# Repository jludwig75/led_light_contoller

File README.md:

# LED Light Controller #
This is a simple controller for for cheap 2-wire LED strings. These strings are setup with LED's alternating polarity along the two wires. Current inone direction lights every other LED and current in the other direction lights the other LED's in the string. These LED strings are really cheap and often sold with remote controls to control the lighting. The battery life is terrible and the light patterns selections weren't that great. I wrote this Arduino sketch for and ESP8266 to control the LED strings. I am using ESP8266 breakouts from Electrodragon that include a USB port for programming and power. I am also using a DRV8833 H-bridge to controll the LED's powered by the 5V pin from the USB connector to the Electordragon board.

The sketch includes a web server used to controll the light pattern. Each board controls two strings (channels) independently. Note that the sketch is written to switch polarity every 10ms (100Hz). This allows the strings to appear to be contantly lit in both directions.

## Components  ##
- Electrodragon board link: https://www.electrodragon.com/product/esp8266-smd-adapter-breakout-board-r3/
- DRV8833 Link: https://www.amazon.com/gp/product/B08FJ3TX3Z/ref=ppx_yo_dt_b_asin_title_o01_s00?ie=UTF8&psc=1
- LED Light Strings: https://www.amazon.com/gp/product/B07QC65SZP/ref=ppx_yo_dt_b_asin_title_o04_s00?ie=UTF8&psc=1

## Schematic ##

## PCB Board ##

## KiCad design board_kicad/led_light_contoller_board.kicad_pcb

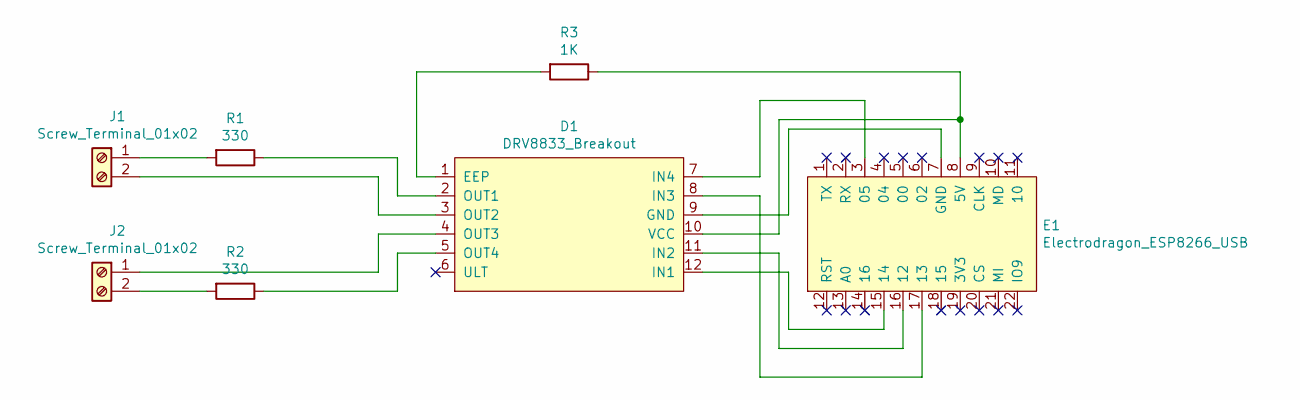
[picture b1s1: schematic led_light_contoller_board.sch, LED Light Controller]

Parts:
D1: DRV8833_Breakout
E1: Electrodragon_ESP8266_USB; Electrodragon ESP8266 USB
J1, J2: Screw_Terminal_01x02; Screw_Terminal_2.54mm
R1, R2: 330; R_Axial_DIN0207_L6.3mm_D2.5mm_P10.16mm_Horizontal
R3: 1K; R_Axial_DIN0207_L6.3mm_D2.5mm_P10.16mm_Horizontal

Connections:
unnamed: D1.1 (EEP), R3.2
unnamed: D1.2 (OUT1), R1.1
unnamed: D1.3 (OUT2), J1.2
unnamed: D1.4 (OUT3), J2.1
unnamed: D1.5 (OUT4), R2.1
unnamed: D1.7 (IN4), E1.3 (05)
unnamed: D1.8 (IN3), E1.17 (13)
unnamed: D1.9 (GND), E1.7 (GND)
unnamed: D1.10 (VCC), E1.8 (5V), R3.1
unnamed: D1.11 (IN2), E1.16 (12)
unnamed: D1.12 (IN1), E1.15 (14)
unnamed: J1.1, R1.2
unnamed: J2.2, R2.2

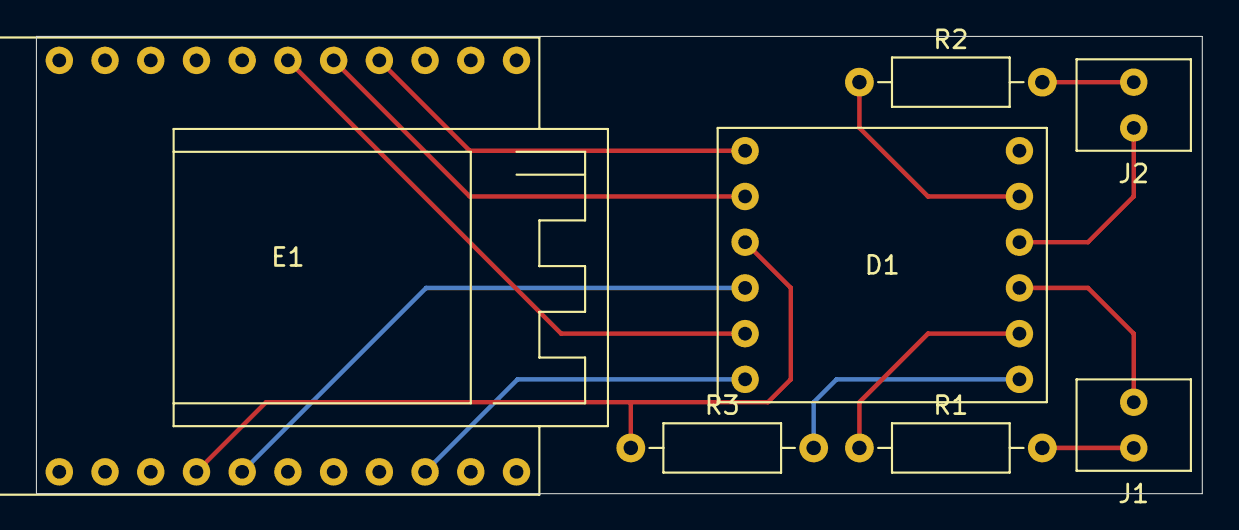
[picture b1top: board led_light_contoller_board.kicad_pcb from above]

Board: 2 copper layers, 64.8 x 25.4 mm, 7 parts (0 on the bottom side), 13 nets.

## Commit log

2020-12-24 Created repo
2020-12-24 Add .gitignore
2020-12-25 Started basic framework for board firmware
2020-12-25 Started channel mock
2020-12-25 Work on web server
2020-12-25 Got webserver working with mock LED channels
2020-12-25 LED controller and channel
2020-12-25 Set default mode to constant. Don't show any mode in UI if change mode failed
2020-12-25 Removed invalid comment
2020-12-25 Improved channel list UI
2020-12-25 Improved button appearance
2020-12-25 Use jQuery UI for better radio buttons
2020-12-25 Left align text on radio buttons
2020-12-25 Don't reinvent the wheel. Fix webpage title
2020-12-26 Got something testable together
2020-12-26 Made web server a class like it should have been
2020-12-26 Set initial LED string state
2020-12-26 Got bidirectional LED signal working
    Had to disable web page refresh because it perturbs the timer.
    Need to get some kind of HW timer working, but it is REALLY touchy.
    Maybe adding a 3v3 arduino mini might be better and it can implement
    the timer and drive the H bridge.
2020-12-27 Finished mode functions
2020-12-27 Tweaked fade function timing
2020-12-27 Added slow pulse mode
2020-12-27 Added star light function
2020-12-28 Swith terminology from direction to stripe. Issue #2
2020-12-28 Persist channel mode to flash. Issue #4
2020-12-28 Separated side 0 and 1 brightness levels. Made string functions return separate side brightness levels. Fixes issue #1
2020-12-30 Added schematic and PCB to project
2020-12-30 Added README
2021-01-08 Split up platformio.ini config and moved hostname to config file
2021-01-12 Added config for 3rd light controller
